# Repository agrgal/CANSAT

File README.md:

<center></center>

# CANSAT - A4I y HEXACT
Proyectos CANSAT IES Seritium, año 2022 y 2023, presentados a los lanzamientos en la comunidad autónoma de Andalucía en Coria del Río y Antequera. Copia pública

# Reconocimiento
[CANSAT IES Seritium](https://github.com/CANSAT) © 2023 by Alejandro Chacón, David González, Antonio Jesús Suarez, Adrián Durán, Miriam Ganaza, Iker Espinosa y Aurelio Gallardo is licensed under [CC BY-NC-SA 4.0 ](http://creativecommons.org/licenses/by-nc-sa/4.0/?ref=chooser-v1)

# ¿Qué es?
El proyecto CANSAT (HEXACT en 2023, A4I en 2022) llevado a cabo por los alumnos Alejandro Chacón, David González, Antonio Jesús Suarez, Adrián Durán, Miriam Ganaza e Iker Espinosa del IES Seritium. Como mentor, Aurelio Gallardo. 

# ¿Qué contiene este documento?
Informe crítico de diseño y todo aquel material elaborado para llevar a cabo el proyecto (diseño, pruebas, programación, informes, resultados) de nuestra participación en las pruebas andaluzas de los años 2022 y 2023

# Material gráfico
+ [Vídeo presentación del proyecto 2023](https://youtu.be/i_LCr1teCZs?si=MErtpM3VWjnIBio4)
+ [Lanzamiento Mayo 2023](https://www.youtube.com/watch?v=RIHoM7wkHl4)
+ [Noticia diario de Jerez](https://www.diariodejerez.es/jerez/IES-Seritium-Agencia-Espacial-Europea-cansat_0_1791421220.html)
+ [CANSAT 2022](https://www.seritium.es/wordpress/index.php/2022/03/24/proyecto-cansat-2022/)

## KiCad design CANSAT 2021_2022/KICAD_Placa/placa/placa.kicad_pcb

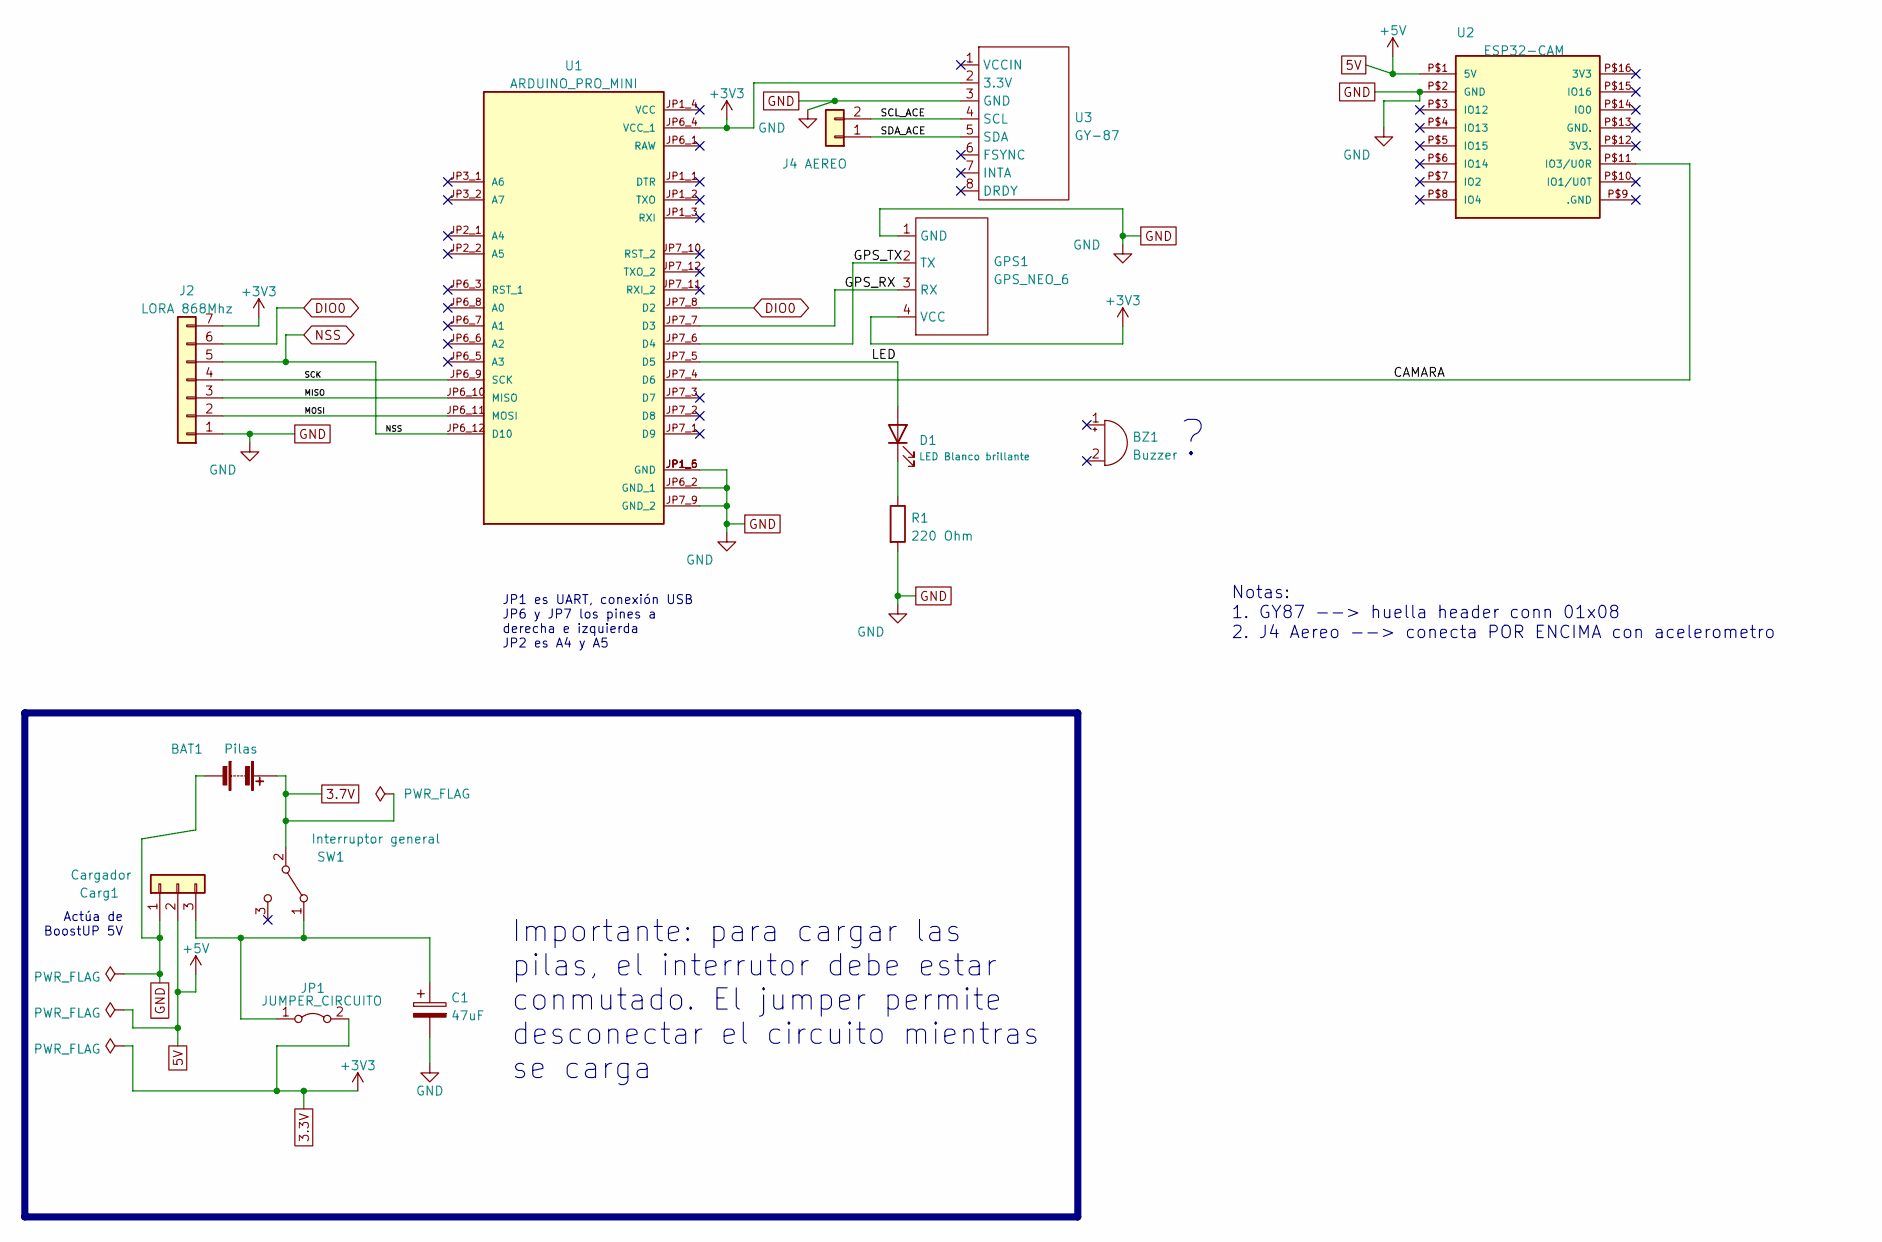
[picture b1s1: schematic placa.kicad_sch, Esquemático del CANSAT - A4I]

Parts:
BAT1: Pilas; PinHeader_1x02_P2.54mm_Vertical_SMD_Pin1Left
BZ1: Buzzer; Buzzer_15x7.5RM7.6
C1: 47uF; CP_Radial_D8.0mm_P3.50mm
Carg1: Cargador; SolderWire-0.25sqmm_1x03_P4.2mm_D0.65mm_OD1.7mm_Relief
D1: LED Blanco brillante; LED_D5.0mm_Horizontal_O3.81mm_Z3.0mm
GPS1: GPS_NEO_6; PinHeader_1x04_P2.54mm_Vertical
J2: LORA 868Mhz; PinHeader_1x07_P2.54mm_Vertical
J4: AEREO; PinHeader_1x02_P2.54mm_Vertical
JP1: JUMPER_CIRCUITO; PinHeader_1x02_P2.54mm_Vertical
R1: 220 Ohm; R_Axial_DIN0414_L11.9mm_D4.5mm_P5.08mm_Vertical
SW1: Interruptor general; R_Axial_Power_L20.0mm_W6.4mm_P5.08mm_Vertical
U1: ARDUINO_PRO_MINI; MODULE_ARDUINO_PRO_MINI; PARTREV N/A
U2: ESP32-CAM
U3: GY-87; PinHeader_1x08_P2.54mm_Vertical

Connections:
3.3V: GPS1.4 (VCC), J2.7, JP1.2 (B), U1.JP6_4 (VCC_1), U3.2 (3.3V)
3.7V: BAT1.1 (+), SW1.2 (B)
5V: Carg1.2, U2.P$1 (5V)
/MISO: J2.3, U1.JP6_10 (MISO)
/MOSI: J2.2, U1.JP6_11 (MOSI)
/SCK: J2.4, U1.JP6_9 (SCK)
DIO0: J2.6, U1.JP7_8 (D2)
GND: BAT1.2 (-), C1.2, Carg1.1, GPS1.1 (GND), J2.1, R1.2, U1.JP1_5 (GND), U1.JP1_6 (GND), U1.JP6_2 (GND_1), U1.JP7_9 (GND_2), U2.P$2 (GND), U3.3 (GND)
NSS: J2.5, U1.JP6_12 (D10)
unnamed: C1.1, Carg1.3, JP1.1 (A), SW1.1 (A)
unnamed: D1.1 (K), R1.1
unnamed: D1.2 (A), U1.JP7_5 (D5)
unnamed: GPS1.2 (TX), U1.JP7_6 (D4)
unnamed: GPS1.3 (RX), U1.JP7_7 (D3)
unnamed: J4.1, U3.5 (SDA)
unnamed: J4.2, U3.4 (SCL)
unnamed: U1.JP7_4 (D6), U2.P$11 (IO3/U0R)

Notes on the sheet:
JP1 es UART, conexión USB JP6 y JP7 los pines a derecha e izquierda JP2 es A4 y A5
Importante: para cargar las pilas, el interrutor debe estar conmutado. El jumper permite desconectar el circuito mientras se carga
Notas: 1. GY87 --> huella header conn 01x08 2. J4 Aereo --> conecta POR ENCIMA con acelerometro
Actúa de BoostUP 5V

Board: 2 copper layers, 13 parts (0 on the bottom side), 17 nets, no tracks yet.

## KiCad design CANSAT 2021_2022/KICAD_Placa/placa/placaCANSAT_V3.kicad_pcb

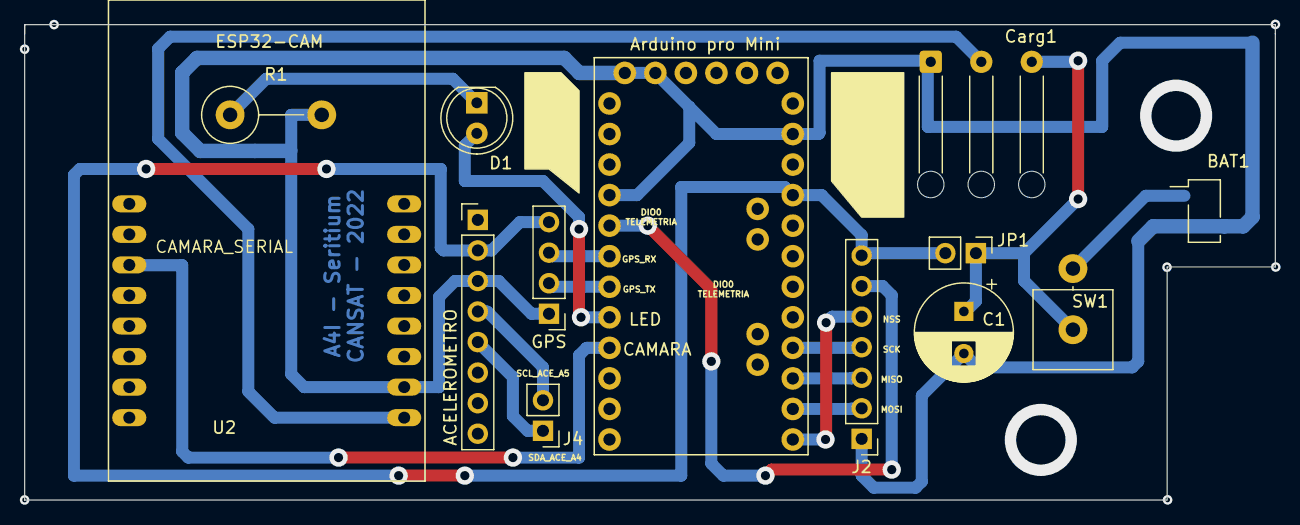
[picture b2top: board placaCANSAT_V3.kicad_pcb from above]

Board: 2 copper layers, 104.0 x 39.5 mm, 13 parts (0 on the bottom side), 17 nets.

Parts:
ACELEROMETRO: GY-87; PinHeader_1x08_P2.54mm_Vertical
Arduino pro Mini: ARDUINO_PRO_MINI; MODULE_ARDUINO_PRO_MINI
BAT1: Pilas; PinHeader_1x02_P2.54mm_Vertical_SMD_Pin1Left
C1: 47uF; CP_Radial_D8.0mm_P3.50mm
Carg1: Cargador; SolderWire-0.25sqmm_1x03_P4.2mm_D0.65mm_OD1.7mm_Relief
D1: LED Blanco brillante; LED_D5.0mm
GPS: GPS_NEO_6; PinHeader_1x04_P2.54mm_Vertical
J2: LORA 868Mhz; PinHeader_1x07_P2.54mm_Vertical
J4: AEREO; PinHeader_1x02_P2.54mm_Vertical
JP1: JUMPER_CIRCUITO; PinHeader_1x02_P2.54mm_Vertical
R1: 220 Ohm; R_Axial_DIN0414_L11.9mm_D4.5mm_P7.62mm_Vertical
SW1: Interruptor general; R_Axial_Power_L20.0mm_W6.4mm_P5.08mm_Vertical
U2: ESP32-CAM

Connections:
3.3V: ACELEROMETRO.2 (3.3V), Arduino pro Mini.JP6_4 (VCC_1), GPS.4 (VCC), J2.7, JP1.2 (B)
3.7V: BAT1.1 (+), SW1.2 (B)
5V: Carg1.2, U2.P$1 (5V)
/CAMARA: Arduino pro Mini.JP7_4 (D6), U2.P$11 (IO3/U0R)
/GPS_RX: Arduino pro Mini.JP7_7 (D3), GPS.3 (RX)
/GPS_TX: Arduino pro Mini.JP7_6 (D4), GPS.2 (TX)
/LED: Arduino pro Mini.JP7_5 (D5), D1.2 (A)
/MISO: Arduino pro Mini.JP6_10 (MISO), J2.3
/MOSI: Arduino pro Mini.JP6_11 (MOSI), J2.2
/SCK: Arduino pro Mini.JP6_9 (SCK), J2.4
/SCL_ACE: ACELEROMETRO.4 (SCL), J4.2
/SDA_ACE: ACELEROMETRO.5 (SDA), J4.1
DIO0: Arduino pro Mini.JP7_8 (D2), J2.6
GND: ACELEROMETRO.3 (GND), Arduino pro Mini.JP1_5 (GND), Arduino pro Mini.JP1_6 (GND), Arduino pro Mini.JP6_2 (GND_1), Arduino pro Mini.JP7_9 (GND_2), BAT1.2 (-), C1.2, Carg1.1, GPS.1 (GND), J2.1, R1.2, U2.P$2 (GND)
NSS: Arduino pro Mini.JP6_12 (D10), J2.5
unnamed: C1.1, Carg1.3, JP1.1 (A), SW1.1 (A)
unnamed: D1.1 (K), R1.1

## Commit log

2024-03-16 CANSAT 2022_2023
    Proyecto CANSAT del año 2022_2023
2024-03-16 CANSAT 2021_2022
    Informe crítico de diseño y material del lanzamiento en 2022. Puebla del Río.
2025-08-20 probando
    probando
2025-08-20 Delete probandoAlgo.txt
    Delete probando algo
